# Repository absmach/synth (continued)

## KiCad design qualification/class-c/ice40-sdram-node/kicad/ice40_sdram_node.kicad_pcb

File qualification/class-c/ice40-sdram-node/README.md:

# iCE40HX4K SDR SDRAM node with a USB-C power input (Class C, case 2)

An iCE40HX4K FPGA in a 144-pin TQFP (0.5 mm pitch) with a 64 Mbit SDR SDRAM (ISSI IS42S16400J, TSOP-II-54), an SPI boot flash, a 1x6 programming header and three status LEDs, powered from a USB-C receptacle (5 V only), on six copper layers. It answers #329 under #40: a board whose memory interface is length- and impedance-sensitive, made by an agent driving `synth mcp`. The interface is a single-data-rate SDRAM driven by a soft controller in the FPGA fabric: there is no DQS strobe, no differential pair and no DDR claim. Jeff Mboya is the independent PCB reviewer as well as the author of this pull request.

## The board

| Group | Parts |
|---|---|
| Power entry | `J1` Korean Hroparts TYPE-C-31-M-12 USB-C receptacle (5 V from VBUS only, D+, D- and SBU unconnected) with `R2` and `R3`, 5.1 k pull-downs on CC1 and CC2; `F1` Bourns MF-MSMF110/16-2 (1.1 A hold, 2.2 A trip, 16 V); `D1` Nexperia PTVS6V0S1UR (6.0 V standoff, 6.67 V minimum breakdown) above the 5.25 V maximum input; `Q1` Vishay SI2301CDS P-MOSFET reverse-polarity stage with `R1`, `C1` |
| 3.3 V | `U1` AMS1117-3.3 with 10 uF capacitors `C2` to `C5` |
| 1.2 V core | `U2` Texas Instruments TLV70012DDCR, TSOT-23-5, with `C6` and `C7`; the PLL supply `VCCPLL` through the ferrite bead `L1` (Murata BLM18AG601SN1D) and `C23` |
| FPGA | `U3` Lattice iCE40HX4K-TQ144, supply decoupling 100 nF `C10` to `C24` |
| SDRAM | `U4` ISSI IS42S16400J-7TLI (64 Mbit, 143 MHz, 3.0 to 3.6 V), decoupling `C30` to `C37`, six 22 ohm series resistors `RS1` to `RS6` at the FPGA end of the command, clock and control lines |
| Configuration | `U5` Winbond W25Q128JVSIQ, SOIC-8 208 mil, master SPI; `R10` and `R11` pull `CRESET_B` and `CDONE` up, `R12` the chip select, `R13` and `R14` the write-protect and hold pins; `J2` 1x6 programming header (SS_B, SCK, SDI, SDO, CRESET_B, GND) |
| Indicators and test points | `D2` red (3.3 V present), `D3` green (CDONE, buffered by the N-MOSFET `Q2` AO3400A because CDONE is open-drain), `D4` green user LED; test points `TP1` to `TP7`; two M2.5 mounting holes at opposite corners |

The iCE40HX4K-TQ144 has 107 user I/O (Lattice DS1040), the part model in [`registry/parts/fpga/ice40hx4k_tq144.synth.toml`](../../../registry/parts/fpga/ice40hx4k_tq144.synth.toml) is built from KiCad's `FPGA_Lattice:ICE40HX4K-TQ144` symbol with the pin functions of that datasheet. The memory pins sit on the FPGA's left side facing the SDRAM, in the order of the SDRAM's near pin row, so the data bus runs straight across with no crossings.

The qualification verdict, measurements, evidence and sign-off are in [`QUALIFICATION.md`](QUALIFICATION.md); how the board was made is in [`PROVENANCE.md`](PROVENANCE.md). Gerber content hash `e4663ac189`.

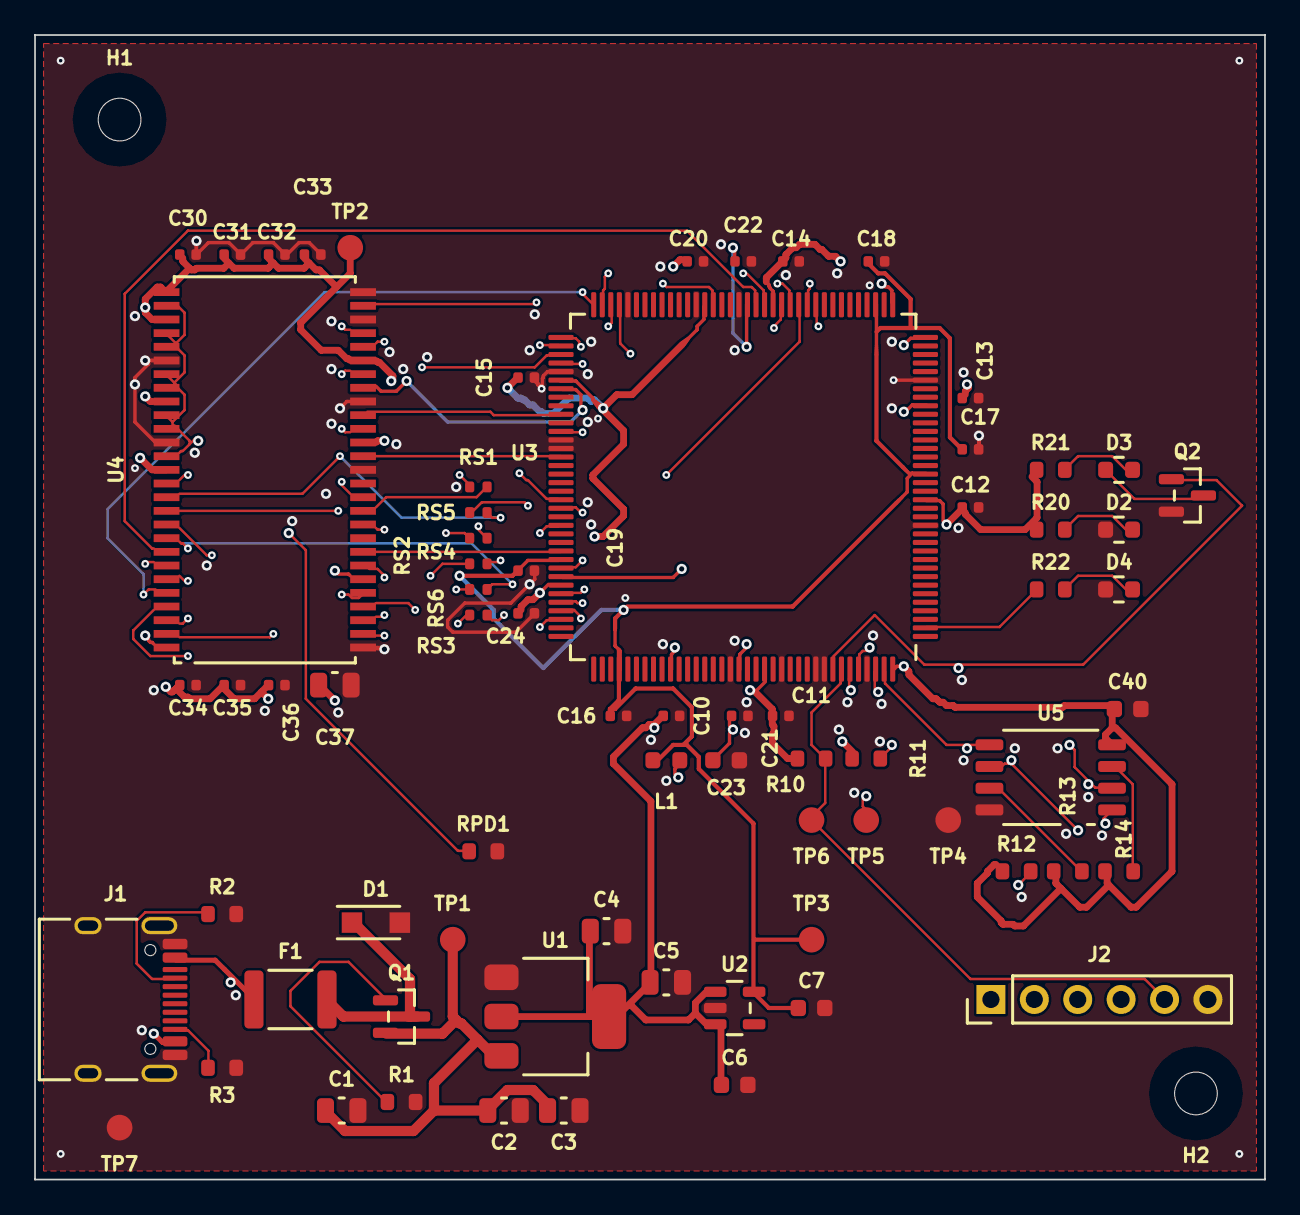
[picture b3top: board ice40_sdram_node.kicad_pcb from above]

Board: 6 copper layers, 72.0 x 67.0 mm, 73 parts (0 on the bottom side), 60 nets.

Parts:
C1, C2, C3, C4, C5, C37: 10uF; C_0805_2012Metric
C6, C7, C23: 1uF; C_0603_1608Metric
C10, C11, C12, C13, C14, C15, C16, C17, C18, C19, C20, C21, C22, C24, C30, C31, C32, C33, C34, C35, C36: 100nF; C_0402_1005Metric
C40: 100nF; C_0603_1608Metric
D1: PTVS6V0S1UR; Nexperia_CFP3_SOD-123W
D2: 0603-RED; LED_0603_1608Metric
D3, D4: 0603-GREEN; LED_0603_1608Metric
F1: MF-MSMF110/16-2; Fuse_1812_4532Metric
H1, H2: (no value); MountingHole_2.5mm
J1: TYPE-C-31-M-12; USB_C_Receptacle_HRO_TYPE-C-31-M-12
J2: (no value); PinHeader_1x06_P2.54mm_Vertical
L1: (no value); L_0603_1608Metric
Q1: SI2301CDS-T1-GE3; SOT-23
Q2: AO3400A; SOT-23
R1, R10, R11, R12, R13, R14: 10k; R_0603_1608Metric
R2, R3: 5.1k; R_0603_1608Metric
R20, R21, R22: 1k; R_0603_1608Metric
RPD1: 10k; R_0603_1608Metric
RS1, RS2, RS3, RS4, RS5, RS6: 22; R_0402_1005Metric
TP1, TP2, TP3, TP4, TP5, TP6, TP7: (no value); TestPoint_Pad_D1.5mm
U1: AMS1117-3.3; SOT-223-3_TabPin2
U2: TLV70012DDCR; TSOT-23-5
U3: ICE40HX4K-TQ144; TQFP-144_20x20mm_P0.5mm
U4: IS42S16400J-7TLI; TSOP-II-54_22.2x10.16mm_P0.8mm
U5: W25Q128JVSIQ; SOIC-8_5.3x5.3mm_P1.27mm

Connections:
+1V2: C7.1, C16.1, C17.1, C18.1, C19.1, L1.1, TP3.1, U2.5, U3.27, U3.40, U3.92, U3.111
+3V3: C4.1, C5.1, C6.1, C10.1, C11.1, C12.1, C13.1, C14.1, C15.1, C20.1, C24.1, C30.1, C31.1, C32.1, C33.1, C34.1, C35.1, C36.1, C37.1, C40.1, R10.1, R11.1, R12.1, R13.1, R14.1, R20.1, R21.1, TP2.1, U1.2, U2.1, U2.3, U3.6, U3.30, U3.46, U3.57, U3.72, U3.89, U3.100, U3.108, U3.109, U3.123, U3.131, U4.1, U4.3, U4.9, U4.14, U4.27, U4.43, U4.49, U5.8
+5V: C1.1, C2.1, C3.1, Q1.2, TP1.1, U1.3
CDONE: Q2.1, R11.2, TP5.1, U3.65
CRESET_B: J2.5, R10.2, TP6.1, U3.66
FLASH_HOLD: R14.2, U5.7
FLASH_WP: R13.2, U5.3
GND: C1.2, C2.2, C3.2, C4.2, C5.2, C6.2, C7.2, C10.2, C11.2, C12.2, C13.2, C14.2, C15.2, C16.2, C17.2, C18.2, C19.2, C20.2, C21.2, C22.2, C23.2, C24.2, C30.2, C31.2, C32.2, C33.2, C34.2, C35.2, C36.2, C37.2, C40.2, D1.2, D2.1, D4.1, J1.A1, J1.A12, J1.B1, J1.B12, J1.SH, J2.6, Q2.2, R1.2, R2.2, R3.2, RPD1.2, TP4.1, TP7.1, U1.1, U2.2, U3.5, U3.13, U3.14, U3.53, U3.59, U3.63, U3.64, U3.69, U3.86, U3.103, U3.127, U3.132, U3.140, U4.6, U4.12, U4.28, U4.41, U4.46, U4.52, U4.54, U5.4
LED_DONE_A: D3.2, R21.2
LED_DONE_K: D3.1, Q2.3
LED_PWR: D2.2, R20.2
LED_USER_A: D4.2, R22.2
LED_USER_R: R22.1, U3.74
Q1_GATE: Q1.1, R1.1
SD_A0: U3.144, U4.23
SD_A1: U3.143, U4.24
SD_A2: U3.142, U4.25
SD_A3: U3.141, U4.26
SD_A4: U3.34, U4.29
SD_A5: U3.33, U4.30
SD_A6: U3.32, U4.31
SD_A7: U3.31, U4.32
SD_A8: U3.29, U4.33
SD_A9: U3.28, U4.34
SD_A10: U3.130, U4.22
SD_A11: U3.26, U4.35
SD_BA0: U3.125, U4.20
SD_BA1: U3.124, U4.21
SD_CAS: RS4.2, U4.17
SD_CAS_F: RS4.1, U3.119
SD_CK: RS1.2, U4.38
SD_CKE: RS6.2, U4.37
SD_CKE_F: RS6.1, U3.23
SD_CK_F: RS1.1, U3.21
SD_CS: RS2.2, U4.19
SD_CS_F: RS2.1, U3.121
SD_DQ8: U3.15, U4.42
SD_DQ9: U3.12, U4.44
SD_DQ10: U3.10, U4.45
SD_DQ11: U3.7, U4.47
SD_DQ12: U3.4, U4.48
SD_DQ13: U3.3, U4.50
SD_DQ14: U3.2, U4.51
SD_DQ15: U3.1, U4.53
SD_DQ_LO: RPD1.1, U4.2, U4.4, U4.5, U4.7, U4.8, U4.10, U4.11, U4.13
SD_LDQM: U3.122, U4.15
SD_RAS: RS3.2, U4.18
SD_RAS_F: RS3.1, U3.120
SD_UDQM: U3.20, U4.39
SD_WE: RS5.2, U4.16
SD_WE_F: RS5.1, U3.118
SPI_SCK: J2.2, U3.70, U5.6
SPI_SDI: J2.3, U3.68, U5.2
SPI_SDO: J2.4, U3.67, U5.5
SPI_SS_B: J2.1, R12.2, U3.71, U5.1
USB_CC1: J1.A5, R2.1
USB_CC2: J1.B5, R3.1
VCCPLL: C21.1, C22.1, C23.1, L1.2, U3.54, U3.126
VIN_FUSED: D1.1, F1.2, Q1.3
VIN_RAW: F1.1, J1.A4, J1.A9, J1.B4, J1.B9

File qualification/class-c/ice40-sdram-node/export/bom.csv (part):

refdes,value,kind,description,kicad_symbol,kicad_footprint,lcsc_pn,mpn
C1,10uF,capacitor,"Generic 0805 MLCC, X7R/X5R, any value",Device:C,Capacitor_SMD:C_0805_2012Metric,,
C10,100nF,capacitor,"Generic 0402 MLCC, X7R/X5R, any value",Device:C,Capacitor_SMD:C_0402_1005Metric,,
C11,100nF,capacitor,"Generic 0402 MLCC, X7R/X5R, any value",Device:C,Capacitor_SMD:C_0402_1005Metric,,
C12,100nF,capacitor,"Generic 0402 MLCC, X7R/X5R, any value",Device:C,Capacitor_SMD:C_0402_1005Metric,,
C13,100nF,capacitor,"Generic 0402 MLCC, X7R/X5R, any value",Device:C,Capacitor_SMD:C_0402_1005Metric,,
C14,100nF,capacitor,"Generic 0402 MLCC, X7R/X5R, any value",Device:C,Capacitor_SMD:C_0402_1005Metric,,
C15,100nF,capacitor,"Generic 0402 MLCC, X7R/X5R, any value",Device:C,Capacitor_SMD:C_0402_1005Metric,,
C16,100nF,capacitor,"Generic 0402 MLCC, X7R/X5R, any value",Device:C,Capacitor_SMD:C_0402_1005Metric,,
C17,100nF,capacitor,"Generic 0402 MLCC, X7R/X5R, any value",Device:C,Capacitor_SMD:C_0402_1005Metric,,
C18,100nF,capacitor,"Generic 0402 MLCC, X7R/X5R, any value",Device:C,Capacitor_SMD:C_0402_1005Metric,,
C19,100nF,capacitor,"Generic 0402 MLCC, X7R/X5R, any value",Device:C,Capacitor_SMD:C_0402_1005Metric,,
C2,10uF,capacitor,"Generic 0805 MLCC, X7R/X5R, any value",Device:C,Capacitor_SMD:C_0805_2012Metric,,
C20,100nF,capacitor,"Generic 0402 MLCC, X7R/X5R, any value",Device:C,Capacitor_SMD:C_0402_1005Metric,,
C21,100nF,capacitor,"Generic 0402 MLCC, X7R/X5R, any value",Device:C,Capacitor_SMD:C_0402_1005Metric,,
C22,100nF,capacitor,"Generic 0402 MLCC, X7R/X5R, any value",Device:C,Capacitor_SMD:C_0402_1005Metric,,
C23,1uF,capacitor,"Generic 0603 MLCC, X7R/X5R, any value",Device:C,Capacitor_SMD:C_0603_1608Metric,,
C24,100nF,capacitor,"Generic 0402 MLCC, X7R/X5R, any value",Device:C,Capacitor_SMD:C_0402_1005Metric,,
C3,10uF,capacitor,"Generic 0805 MLCC, X7R/X5R, any value",Device:C,Capacitor_SMD:C_0805_2012Metric,,
C30,100nF,capacitor,"Generic 0402 MLCC, X7R/X5R, any value",Device:C,Capacitor_SMD:C_0402_1005Metric,,
C31,100nF,capacitor,"Generic 0402 MLCC, X7R/X5R, any value",Device:C,Capacitor_SMD:C_0402_1005Metric,,
C32,100nF,capacitor,"Generic 0402 MLCC, X7R/X5R, any value",Device:C,Capacitor_SMD:C_0402_1005Metric,,
C33,100nF,capacitor,"Generic 0402 MLCC, X7R/X5R, any value",Device:C,Capacitor_SMD:C_0402_1005Metric,,
C34,100nF,capacitor,"Generic 0402 MLCC, X7R/X5R, any value",Device:C,Capacitor_SMD:C_0402_1005Metric,,
C35,100nF,capacitor,"Generic 0402 MLCC, X7R/X5R, any value",Device:C,Capacitor_SMD:C_0402_1005Metric,,
C36,100nF,capacitor,"Generic 0402 MLCC, X7R/X5R, any value",Device:C,Capacitor_SMD:C_0402_1005Metric,,
C37,10uF,capacitor,"Generic 0805 MLCC, X7R/X5R, any value",Device:C,Capacitor_SMD:C_0805_2012Metric,,
C4,10uF,capacitor,"Generic 0805 MLCC, X7R/X5R, any value",Device:C,Capacitor_SMD:C_0805_2012Metric,,
C40,100nF,capacitor,"Generic 0603 MLCC, X7R/X5R, any value",Device:C,Capacitor_SMD:C_0603_1608Metric,,
C5,10uF,capacitor,"Generic 0805 MLCC, X7R/X5R, any value",Device:C,Capacitor_SMD:C_0805_2012Metric,,
C6,1uF,capacitor,"Generic 0603 MLCC, X7R/X5R, any value",Device:C,Capacitor_SMD:C_0603_1608Metric,,
C7,1uF,capacitor,"Generic 0603 MLCC, X7R/X5R, any value",Device:C,Capacitor_SMD:C_0603_1608Metric,,
D1,PTVS6V0S1UR,diode,"Nexperia PTVS6V0S1UR 400 W unidirectional TVS, 6.0 V standoff, SOD123W, for VBUS and CC",Device:D_Zener,Diode_SMD:Nexperia_CFP3_SOD-123W,,PTVS6V0S1UR
D2,0603-RED,diode,"Red LED, 0603 package, ~2.0V Vf",Device:LED,LED_SMD:LED_0603_1608Metric,C2286,0603-RED
D3,0603-GREEN,diode,"Green LED, 0603 package, ~2.2V Vf",Device:LED,LED_SMD:LED_0603_1608Metric,C72043,0603-GREEN
D4,0603-GREEN,diode,"Green LED, 0603 package, ~2.2V Vf",Device:LED,LED_SMD:LED_0603_1608Metric,C72043,0603-GREEN
F1,MF-MSMF110/16-2,fuse,"Bourns MF-MSMF110/16-2 resettable fuse, 1.1 A hold, 16 V, 1812",Device:Polyfuse,Fuse:Fuse_1812_4532Metric,C210834,MF-MSMF110/16-2
H1,(no value),mounting_hole,M2.5 non-plated mounting hole (NPTH) for a board corner,Mechanical:MountingHole,MountingHole:MountingHole_2.5mm,,
H2,(no value),mounting_hole,M2.5 non-plated mounting hole (NPTH) for a board corner,Mechanical:MountingHole,MountingHole:MountingHole_2.5mm,,
J1,TYPE-C-31-M-12,connector,"USB-C receptacle, 24-pin SMD. Modelled here with primary and mirrored power/ground/data pins for full pad coverage.",Connector:USB_C_Receptacle,Connector_USB:USB_C_Receptacle_HRO_TYPE-C-31-M-12,C165948,TYPE-C-31-M-12
J2,(no value),connector,"1x6 through-hole pin header, 2.54 mm pitch, vertical, hand-fitted iCE40 SPI programming port (SPI_SS_B, SPI_SCK, SPI_SDI, SPI_SDO, CRESET_B, GND). No current rating asserted; no MPN or LCSC number asserted.",Connector_Generic:Conn_01x06,Connector_PinHeader_2.54mm:PinHeader_1x06_P2.54mm_Vertical,,
L1,(no value),inductor,"0603 ferrite bead, 600Ω @ 100MHz — EMI suppression",Device:FerriteBead,Inductor_SMD:L_0603_1608Metric,,
Q1,SI2301CDS-T1-GE3,transistor,"Vishay Si2301 P-channel power MOSFET, SOT-23",Transistor_FET:Si2301CDS,Package_TO_SOT_SMD:SOT-23,C10487,SI2301CDS-T1-GE3
Q2,AO3400A,transistor,"Alpha&Omega AO3400A 30 V N-channel MOSFET, SOT-23: ID 5.7 A at 25 C, Rds(on) under 26.5 mOhm at Vgs 10 V, 32 mOhm at 4.5 V and 48 mOhm at 2.5 V, Vgs +/-12 V",Transistor_FET:AO3400A,Package_TO_SOT_SMD:SOT-23,,AO3400A
R1,10k,resistor,"Generic 0603 thick-film resistor, any value",Device:R_US,Resistor_SMD:R_0603_1608Metric,,
R10,10k,resistor,"Generic 0603 thick-film resistor, any value",Device:R_US,Resistor_SMD:R_0603_1608Metric,,
R11,10k,resistor,"Generic 0603 thick-film resistor, any value",Device:R_US,Resistor_SMD:R_0603_1608Metric,,
R12,10k,resistor,"Generic 0603 thick-film resistor, any value",Device:R_US,Resistor_SMD:R_0603_1608Metric,,
R13,10k,resistor,"Generic 0603 thick-film resistor, any value",Device:R_US,Resistor_SMD:R_0603_1608Metric,,
R14,10k,resistor,"Generic 0603 thick-film resistor, any value",Device:R_US,Resistor_SMD:R_0603_1608Metric,,
R2,5.1k,resistor,"Generic 0603 thick-film resistor, any value",Device:R_US,Resistor_SMD:R_0603_1608Metric,,
R20,1k,resistor,"Generic 0603 thick-film resistor, any value",Device:R_US,Resistor_SMD:R_0603_1608Metric,,
R21,1k,resistor,"Generic 0603 thick-film resistor, any value",Device:R_US,Resistor_SMD:R_0603_1608Metric,,
R22,1k,resistor,"Generic 0603 thick-film resistor, any value",Device:R_US,Resistor_SMD:R_0603_1608Metric,,
R3,5.1k,resistor,"Generic 0603 thick-film resistor, any value",Device:R_US,Resistor_SMD:R_0603_1608Metric,,
RPD1,10k,resistor,"Generic 0603 thick-film resistor, any value",Device:R_US,Resistor_SMD:R_0603_1608Metric,,
RS1,22,resistor,"Generic 0402 thick-film resistor, any value",Device:R_US,Resistor_SMD:R_0402_1005Metric,,
RS2,22,resistor,"Generic 0402 thick-film resistor, any value",Device:R_US,Resistor_SMD:R_0402_1005Metric,,
RS3,22,resistor,"Generic 0402 thick-film resistor, any value",Device:R_US,Resistor_SMD:R_0402_1005Metric,,
RS4,22,resistor,"Generic 0402 thick-film resistor, any value",Device:R_US,Resistor_SMD:R_0402_1005Metric,,
RS5,22,resistor,"Generic 0402 thick-film resistor, any value",Device:R_US,Resistor_SMD:R_0402_1005Metric,,
RS6,22,resistor,"Generic 0402 thick-film resistor, any value",Device:R_US,Resistor_SMD:R_0402_1005Metric,,
TP1,(no value),testpoint,"SMD test point pad, 1.5 mm — probe point for a net",Connector:TestPoint,TestPoint:TestPoint_Pad_D1.5mm,,
TP2,(no value),testpoint,"SMD test point pad, 1.5 mm — probe point for a net",Connector:TestPoint,TestPoint:TestPoint_Pad_D1.5mm,,
TP3,(no value),testpoint,"SMD test point pad, 1.5 mm — probe point for a net",Connector:TestPoint,TestPoint:TestPoint_Pad_D1.5mm,,
TP4,(no value),testpoint,"SMD test point pad, 1.5 mm — probe point for a net",Connector:TestPoint,TestPoint:TestPoint_Pad_D1.5mm,,
TP5,(no value),testpoint,"SMD test point pad, 1.5 mm — probe point for a net",Connector:TestPoint,TestPoint:TestPoint_Pad_D1.5mm,,
TP6,(no value),testpoint,"SMD test point pad, 1.5 mm — probe point for a net",Connector:TestPoint,TestPoint:TestPoint_Pad_D1.5mm,,
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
